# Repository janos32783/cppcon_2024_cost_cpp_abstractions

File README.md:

# cppcon_2024
https://www.youtube.com/watch?v=7gz98K_hCEM

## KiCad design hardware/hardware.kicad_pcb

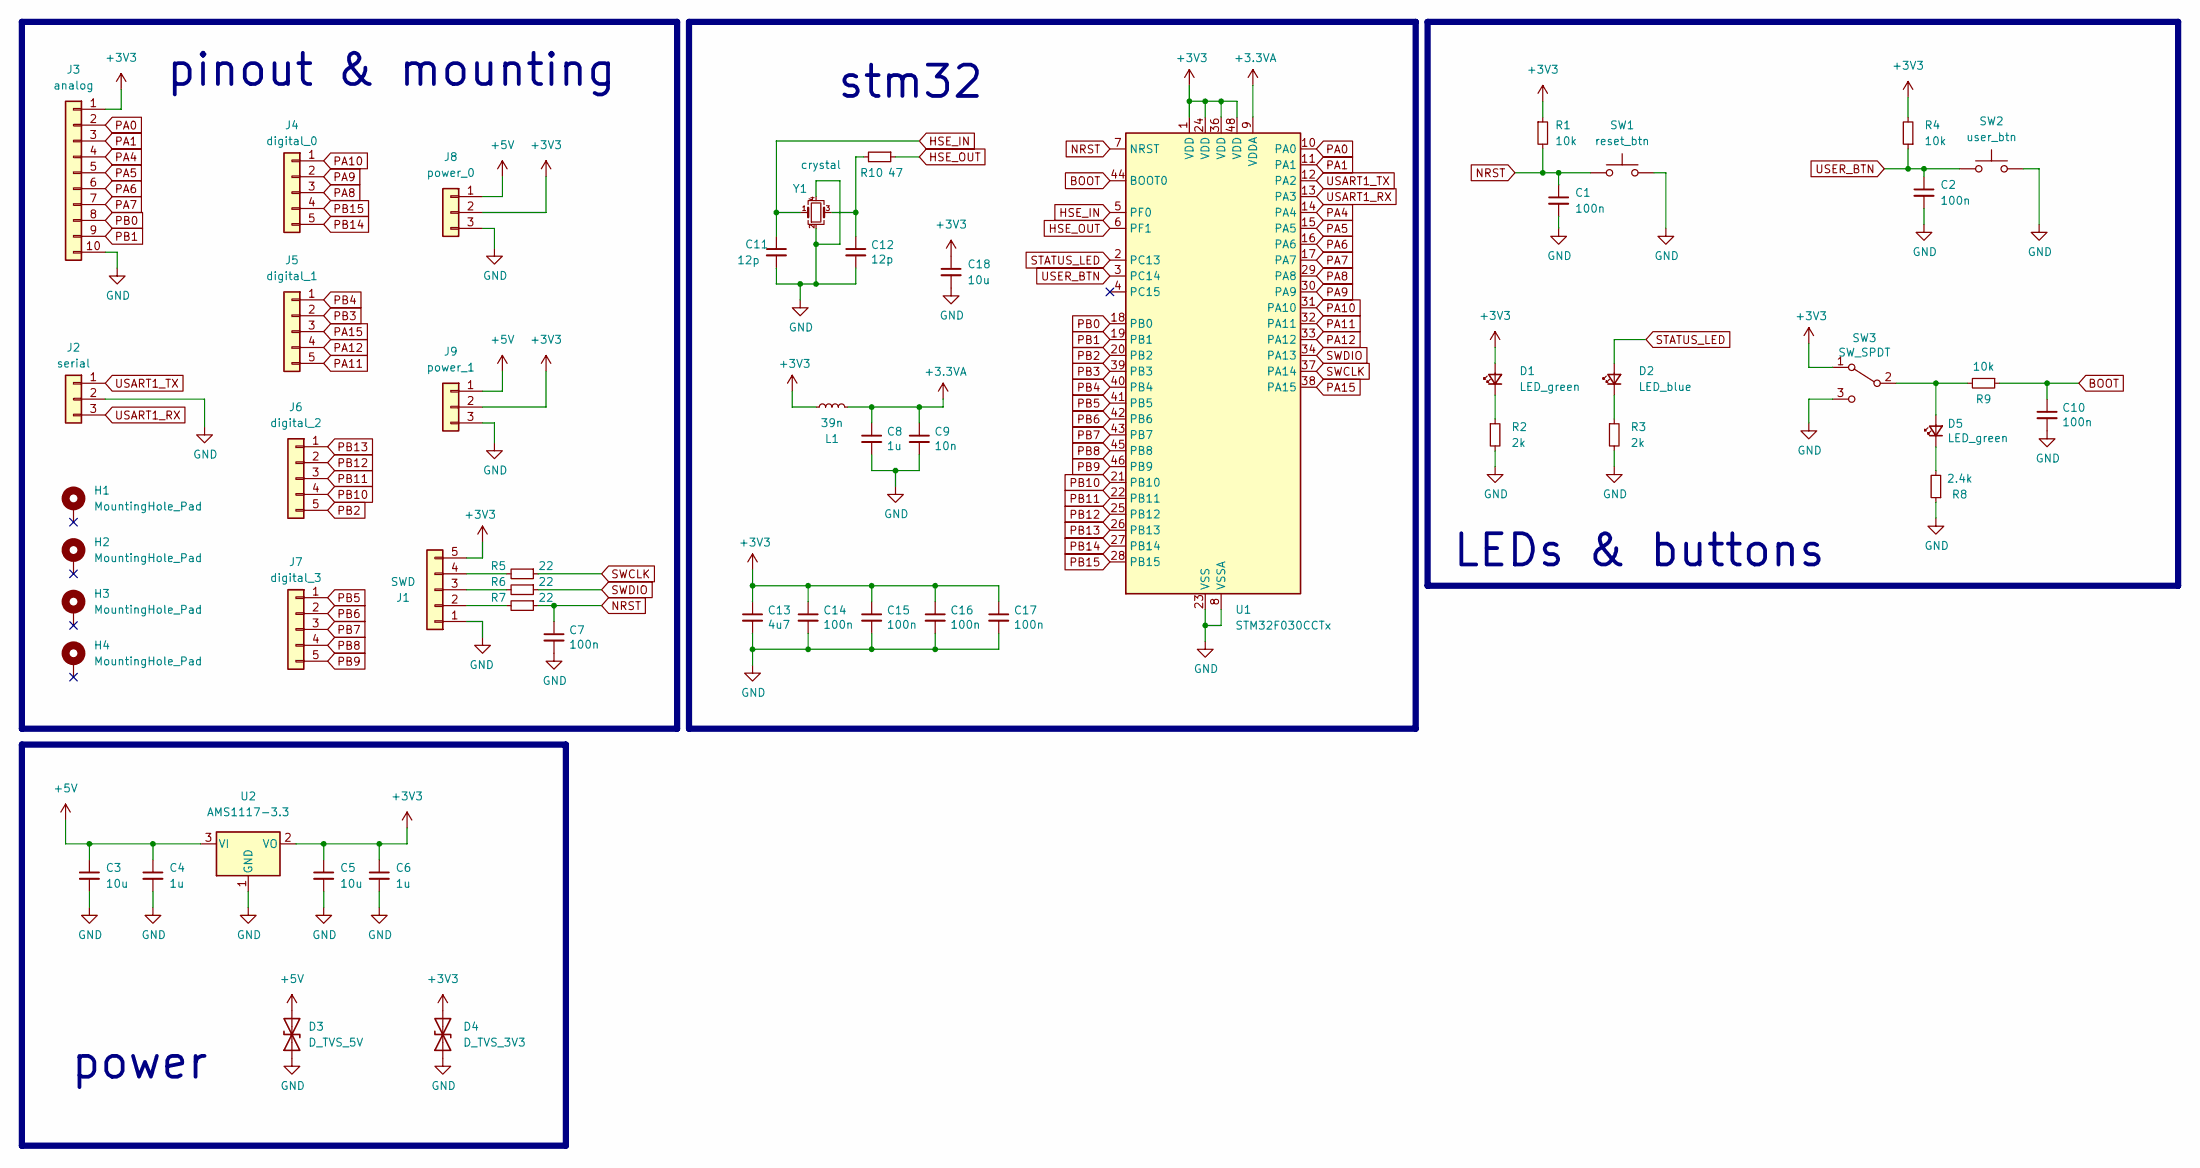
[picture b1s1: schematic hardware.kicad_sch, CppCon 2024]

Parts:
C1, C2, C7, C10, C14, C15, C16, C17: 100n; C_0603_1608Metric
C3, C5, C18: 10u; C_0805_2012Metric
C4, C6, C8: 1u; C_0603_1608Metric
C9: 10n; C_0603_1608Metric
C11, C12: 12p; C_0603_1608Metric
C13: 4u7; C_0603_1608Metric
D1, D5: LED_green; LED_0603_1608Metric
D2: LED_blue; LED_0603_1608Metric
D3: D_TVS_5V; D_SOD-523
D4: D_TVS_3V3; D_SOD-523
H1, H2, H3, H4: MountingHole_Pad; MountingHole_2.2mm_M2_Pad_Via
J1: SWD; PinHeader_1x05_P2.54mm_Vertical
J2: serial; PinHeader_1x03_P2.54mm_Vertical
J3: analog; PinHeader_1x10_P2.54mm_Vertical
J4: digital_0; PinHeader_1x05_P2.54mm_Vertical
J5: digital_1; PinHeader_1x05_P2.54mm_Vertical
J6: digital_2; PinHeader_1x05_P2.54mm_Vertical
J7: digital_3; PinHeader_1x05_P2.54mm_Vertical
J8: power_0; PinHeader_1x03_P2.54mm_Vertical
J9: power_1; PinHeader_1x03_P2.54mm_Vertical
L1: 39n; L_0603_1608Metric
R1, R4, R9: 10k; R_0603_1608Metric
R2, R3: 2k; R_0603_1608Metric
R5, R6, R7: 22; R_0603_1608Metric
R8: 2.4k; R_0603_1608Metric
R10: 47; R_0603_1608Metric
SW1: reset_btn; SW_PUSH_6mm
SW2: user_btn; SW_PUSH_6mm
SW3: SW_SPDT; SW_CK_JS202011AQN_DPDT_Angled
U1: STM32F030CCTx; LQFP-48_7x7mm_P0.5mm
U2: AMS1117-3.3; SOT-223-3_TabPin2
Y1: crystal; Crystal_SMD_3225-4Pin_3.2x2.5mm

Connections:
+3.3VA: C8.1, C9.1, L1.2, U1.9 (VDDA)
+3V3: C5.1, C6.1, C13.1, C14.1, C15.1, C16.1, C17.1, C18.1, D1.2 (A), D4.2 (A2), J1.5, J3.1, J8.2, J9.2, L1.1, R1.1, R4.2, SW3.1 (A), U1.1 (VDD), U1.24 (VDD), U1.36 (VDD), U1.48 (VDD), U2.2 (VO)
+5V: C3.1, C4.1, D3.2 (A2), J8.1, J9.1, U2.3 (VI)
BOOT: C10.1, R9.1, U1.44 (BOOT0)
GND: C1.2, C2.2, C3.2, C4.2, C5.2, C6.2, C7.2, C8.2, C9.2, C10.2, C11.2, C12.2, C13.2, C14.2, C15.2, C16.2, C17.2, C18.2, D3.1 (A1), D4.1 (A1), J1.1, J2.2, J3.10, J8.3, J9.3, R2.2, R3.2, R8.1, SW1.2, SW2.2, SW3.3 (C), U1.8 (VSSA), U1.23 (VSS), U1.35 (VSS), U1.47 (VSS), U2.1 (GND), Y1.2, Y1.4
HSE_IN: C11.1, U1.5 (PF0), Y1.1
HSE_OUT: R10.1, U1.6 (PF1)
NRST: C1.1, C7.1, R1.2, R7.1, SW1.1, U1.7 (NRST)
unnamed: C12.1, R10.2, Y1.3
unnamed: D1.1 (K), R2.1
unnamed: D2.1 (K), R3.1
unnamed: D5.2 (A), R9.2, SW3.2 (B)
unnamed: D5.1 (K), R8.2
unnamed: J1.2, R7.2
unnamed: J1.3, R6.2
unnamed: J1.4, R5.2
PA0: J3.2, U1.10 (PA0)
PA1: J3.3, U1.11 (PA1)
PA4: J3.4, U1.14 (PA4)
PA5: J3.5, U1.15 (PA5)
PA6: J3.6, U1.16 (PA6)
PA7: J3.7, U1.17 (PA7)
PA8: J4.3, U1.29 (PA8)
PA9: J4.2, U1.30 (PA9)
PA10: J4.1, U1.31 (PA10)
PA11: J5.5, U1.32 (PA11)
PA12: J5.4, U1.33 (PA12)
PA15: J5.3, U1.38 (PA15)
PB0: J3.8, U1.18 (PB0)
PB1: J3.9, U1.19 (PB1)
PB2: J6.5, U1.20 (PB2)
PB3: J5.2, U1.39 (PB3)
PB4: J5.1, U1.40 (PB4)
PB5: J7.1, U1.41 (PB5)
PB6: J7.2, U1.42 (PB6)
PB7: J7.3, U1.43 (PB7)
PB8: J7.4, U1.45 (PB8)
PB9: J7.5, U1.46 (PB9)
PB10: J6.4, U1.21 (PB10)
PB11: J6.3, U1.22 (PB11)
PB12: J6.2, U1.25 (PB12)
PB13: J6.1, U1.26 (PB13)
PB14: J4.5, U1.27 (PB14)
PB15: J4.4, U1.28 (PB15)
STATUS_LED: D2.2 (A), U1.2 (PC13)
SWCLK: R5.1, U1.37 (PA14)
SWDIO: R6.1, U1.34 (PA13)
USART1_RX: J2.3, U1.13 (PA3)
USART1_TX: J2.1, U1.12 (PA2)
USER_BTN: C2.1, R4.1, SW2.1, U1.3 (PC14)

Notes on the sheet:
pinout & mounting
stm32
power
LEDs & buttons

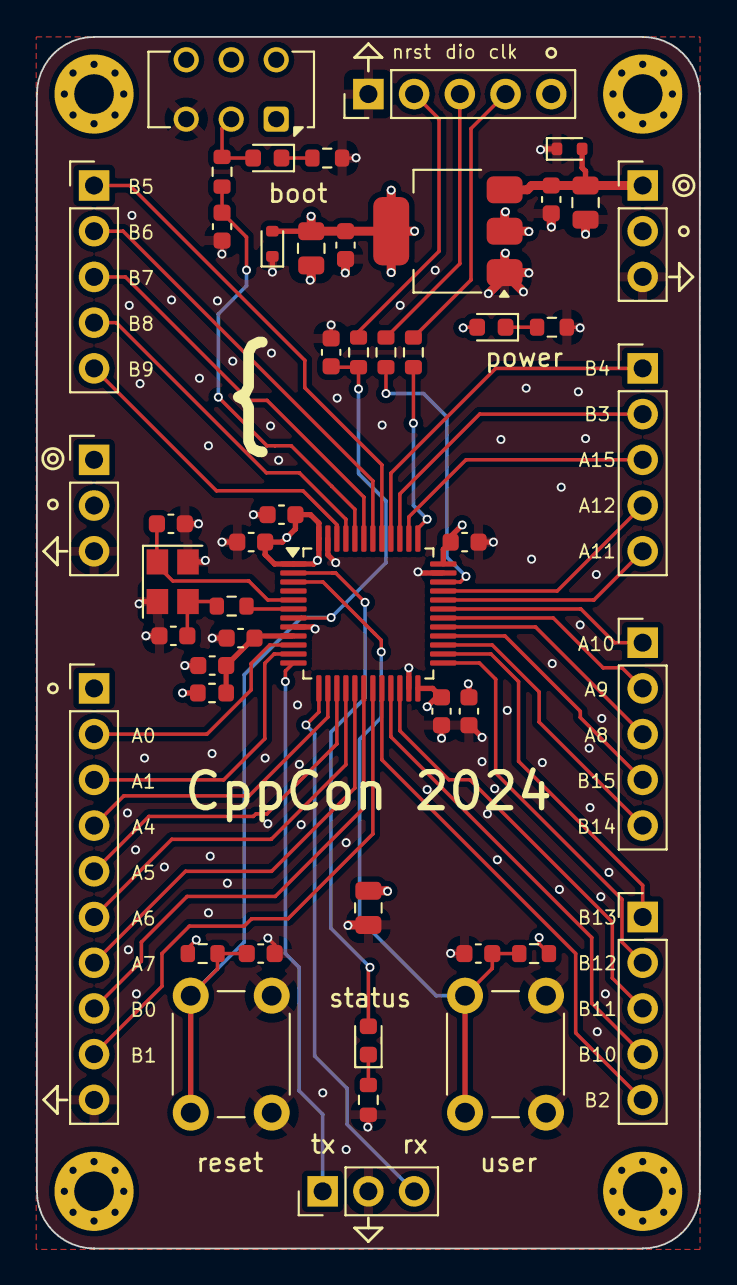
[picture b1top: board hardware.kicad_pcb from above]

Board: 4 copper layers, 36.8 x 67.3 mm, 53 parts (0 on the bottom side), 50 nets.

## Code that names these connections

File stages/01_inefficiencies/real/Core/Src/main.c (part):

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                          |GPIO_PIN_13|GPIO_PIN_14|GPIO_PIN_15|GPIO_PIN_5
                          |GPIO_PIN_6|GPIO_PIN_7|GPIO_PIN_8|GPIO_PIN_9, GPIO_PIN_RESET);

  /*Configure GPIO pin : PC13 */
  GPIO_InitStruct.Pin = GPIO_PIN_13;
  GPIO_InitStruct.Mode = GPIO_MODE_OUTPUT_PP;
  GPIO_InitStruct.Pull = GPIO_NOPULL;
  GPIO_InitStruct.Speed = GPIO_SPEED_FREQ_LOW;
  HAL_GPIO_Init(GPIOC, &GPIO_InitStruct);

  /*Configure GPIO pins : PA0 PA1 PA4 PA8
                           PA9 PA10 PA11 PA12 */
  GPIO_InitStruct.Pin = GPIO_PIN_0|GPIO_PIN_1|GPIO_PIN_4|GPIO_PIN_8
                          |GPIO_PIN_9|GPIO_PIN_10|GPIO_PIN_11|GPIO_PIN_12;
  GPIO_InitStruct.Mode = GPIO_MODE_OUTPUT_PP;
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  GPIO_InitStruct.Speed = GPIO_SPEED_FREQ_LOW;
  HAL_GPIO_Init(GPIOA, &GPIO_InitStruct);

  /*Configure GPIO pins : PB2 PB10 PB11 PB12
                           PB13 PB14 PB15 PB5
                           PB6 PB7 PB8 PB9 */
  GPIO_InitStruct.Pin = GPIO_PIN_2|GPIO_PIN_10|GPIO_PIN_11|GPIO_PIN_12
                          |GPIO_PIN_13|GPIO_PIN_14|GPIO_PIN_15|GPIO_PIN_5
                          |GPIO_PIN_6|GPIO_PIN_7|GPIO_PIN_8|GPIO_PIN_9;
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
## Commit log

2024-05-16 started working on hardware
2024-05-26 ordering first prototype
2024-07-06 updated documents
2024-07-06 extended gitignore
2024-07-06 soldered and tested hardware
2024-07-06 added playground with examples
2024-07-07 updated linker scripts and startup files
2024-07-07 started working on generator
2024-07-07 working on generator
2024-07-08 work in progress
2024-07-08 compiled led blinking project
2024-07-13 added stages based on presentation structure
2024-07-13 cleanup of duplicate files
2024-07-13 using own main
2024-07-13 implemented some other GPIO registers
2024-07-14 added uart config
2024-07-14 started adding HAL initialization steps
2024-07-14 static member function
2024-07-14 added performance measurement
2024-07-14 using common hal
2024-07-15 added cmsis
2024-07-15 moving to another register approach
2024-07-15 using cmsis in systick init
2024-07-16 working on proper initialization
2024-07-16 wokring on system clock initialization
2024-07-16 extended systick to implement chrono behavior
2024-07-16 system clock init work in progress
2024-07-16 pll still missing
2024-07-16 working on PLL
2024-07-17 finished oscillator config
2024-07-17 added clock configuration struct
2024-07-17 working on clock config
2024-07-17 removed chrono
2024-07-17 added error handling, but this results in not inlined functions
2024-07-17 finalized hal init
2024-07-17 started adding gpio init function
2024-07-17 added gpio init
2024-07-17 started adding tests
2024-07-17 added some test cases
2024-07-17 started adding adc init
2024-07-18 adc init work in progress
2024-07-18 finished adc init
2024-07-19 definitely need this linker flag
2024-07-19 removed comment
2024-07-19 started working on merged projects
2024-07-19 removed generator
2024-07-19 added mixed C/C++ project
2024-07-19 removed duplicate
2024-07-19 SysTick_Handler is mine
2024-07-19 merged projects
2024-07-19 added hal::delay_ms
2024-07-19 added adc channel conf struct
2024-07-19 implemented adc channel select
2024-07-19 implemented ADC start
2024-07-19 added adc stop
2024-07-19 added poll for conversoin
2024-07-19 added adc get
2024-07-19 adc as class
2024-07-22 systick fixes
2024-07-22 bugfix
2024-07-22 working example
2024-07-22 removed snprintf and floating point oprtaion
2024-07-22 cleanup
2024-07-23 working on stages 00, 01 and 02
2024-07-23 working on presentation
2024-07-24 extended code for stage encapsulation
2024-07-24 workin on presentation
2024-07-24 readded the original codes
2024-07-24 encapsulation work in progress
2024-07-24 static work in progress
2024-07-24 separated different cases of encapsulation
2024-07-25 encapsulation done for now
2024-07-25 done with encapsulation for now
2024-07-25 updated dynamic polymorphism code
2024-07-25 working on polymorphism
2024-07-25 wokring on polymorphism
2024-07-25 added reference implementation and forced virtual function call
2024-07-25 working on virtual function calls in assembly
2024-07-25 dynamic polymorphism done for now
2024-07-25 done with static polymorphism for now
2024-07-25 going forward with presentation
2024-07-26 working on plotting
2024-07-26 first data
2024-07-26 prepared for measurements
2024-07-26 added inheritance template
2024-07-26 running a measurement
2024-07-27 tests are starting to come together
2024-07-27 added dynamic polymorphism test
2024-07-27 added another test where functions are wrapped into classes
2024-07-27 added another test
2024-07-27 running overnight test
2024-07-28 ran overnight tests
2024-07-28 TEST RESULTS
2024-07-28 analyzing results
2024-07-29 overnight results
2024-07-29 ran tests on laptop as well
2024-07-29 updated plotting script and generated relevant plots
2024-07-29 working on last stage of the presentation
2024-07-31 done measurements on target
2024-07-31 code bloat
2024-07-31 fixed UMLs
2024-07-31 updated LED blinking implementation
2024-08-03 added dev container
2024-08-03 started adjusting presentation on windows -> do not touch it on Linux from now on
2024-08-03 added code for discussion about wrapper
2025-03-16 Update README.md
    Add a link to Marcell's CPPCON talk.

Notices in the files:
stages/01_inefficiencies/real/Core/Src/main.c:
Copyright (c) 2024 STMicroelectronics.
All rights reserved.
This software is licensed under terms that can be found in the LICENSE file
